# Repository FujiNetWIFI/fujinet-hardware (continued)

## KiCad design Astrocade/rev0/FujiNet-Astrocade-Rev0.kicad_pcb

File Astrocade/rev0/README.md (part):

# FujiNet-Astrocade Rev0

All-in-one **Bally Astrocade FujiNet cartridge**: one board in an Astrocade
cassette shell carrying both halves of the Astrocade FujiNet stack.

- **RP2354A** (RP2350A die + 2 MB flash in the package, QFN-60) runs the
  `fujicade` cart firmware from `fujinet-firmware/pico/astrocade`, board
  **`fujicade_rp2354`**. It serves the 8K cart window and the FujiNet
  mailbox straight off the 5 V bus through its 5 V-tolerant pads, with **no
  level shifters**. The pads tolerate 5 V only while IOVDD is powered, so the
  whole RP runs from its own fast LDO (see *Power*).
- **ESP32-S3-WROOM-1-N16R8** runs the **`fujiversal-astrocade`** build of
  fujinet-firmware. The two chips link **on the board over native USB**: the
  S3 is the USB *host* (IO19/IO20) and the RP a CDC device (VID 0xCafe).
  The S3 embeds the RP image and re-flashes it over PICOBOOT whenever it
  changes (`build_pico.py`).
- **USB-C** carries power plus a CP2102N UART with UMH3N auto-program
  (ESP32-S3-DevKitC-1 style) for flashing the S3.
- **microSD** (push-push, SPI on S3 IO38-41). Card detect on IO42 reads
  **low with a card in** (TF-015 drawing: the CD switch closes to the shell).
- **WS2812B-2020** status LED under a light pipe, on **+5V**: its datasheet
  rates VDD 3.7-5.3 V. VIH min is 2.7 V, so the S3's 3.3 V data drives it
  without a level shifter.
- **Buttons:** top-face **RESET** (SW4, resets the RP and the S3), **BOOTSEL**
  pinhole (SW1), S3 **EN/BOOT** (SW2/SW3, board-level).

This revision was audited with kicad-happy and the manufacturer datasheets,
and then redone. The schematic, board and fabrication files are all generated
from `tools/` (see *Regenerating*). The audit is
[`docs/design-review-rev0.md`](docs/design-review-rev0.md).

## Schematic

The schematic is drawn the way the later carts' (2600 Rev1, 7800, SMS, 5200) are:
- **every sheet is the board turned edge-left**: board south -> page left, north -> right, west -> top, east -> bottom;
- each part sits where it is on the board, and `tools/sch_place.py` checks the order;
- **every connection on a sheet is a wire**, flowing left to right from the console to the USB-C.

| Page | Sheet | Contents |
|---|---|---|
| 1 | root | The board outline at 2:1 with each sheet's block over its region; the nine signals between sheets wired; notes |
| 2 | `cart-bus` | The 26-land edge **straight into the RP2354A's GPIO unit**: 22 parallel wires (/CCS, A0-A12, D0-D7), no buffers; /CCS pull-up, the VSENSE divider, activity LED, SELFTEST / DBG_TX pads |
| 3 | `rp-core` | The RP2354A's core unit: every supply pin with its capacitor, the core regulator corner, crystal, SWD, RUN / BOOTSEL / RESET, the USB pair to the S3 |
| 4 | `fujinet` | ESP32-S3, EN / BOOT, microSD, WS2812 status LED |
| 5 | `usb` | USB-C, ESD, CP2102N, esptool's auto-program pair |
| 6 | `power` | Console 5 V / USB VBUS diode-OR, 3.3 V buck, RP LDO |

Rails are power symbols (`CONS_5V`, `VBUS`, `+5V`, `+3V3`, `+3V3_RP`, `DVDD`, `GND`). Sheets join only through hierarchical labels, wired on the root. KiCad names the nets:
- `/cart-bus/CA0` for a net local to its sheet;
- `/S3_EN` for a net joined on the root;
- `GND` for a rail.

The names are frozen in `tools/nets.lock` because the routed board carries them. References are frozen in `tools/refs.lock`.

## Edge port

The cassette edge carries **A0-A12, D0-D7, one pre-decoded active-low
Enable (/CCS), +5V and 3x GND**. There is no /RD, /WR, clock or reset, and
the console only ever *reads* the cart. The RP pin map is exactly
`astrocade_cart.h`:

| RP2354A | Net | Edge (Tilton 1-26) |
|---|---|---|
| GP0-GP12 | CA0-CA12 | A0 9, A1 8, A2 7, A3 6, A4 5, A5 4, A6 3, A7 2, A8 24, A9 23, A10 20, A11 19, A12 22 |
| GP13 | CCS_N (10k pull-up to +3V3_RP) | 21 |
| GP14-GP21 | CD0-CD7 | D0 10, D1 11, D2 12, D3 14, D4 15, D5 16, D6 17, D7 18 |
| GP26 | VSENSE: edge +5V (CONS_5V) through 10k/15k (3.0 V; 6 kOhm, below RP2350-E9's 8.2 kOhm) | 25 |
| GP22 / GP27 | SELFTEST / DBG_TX test pads | - |
| GP25 | green activity LED (330R) | - |

`tools/audit/edge_orientation.py` checks the generated board: land 1 is
**east** in KiCad top view, on B.Cu. That matches Tilton's "looking at the
cart slot, pins 1 to 26 left to right" with the cart inserted label-up.

**The unbuffered bus is safe because the firmware gates it.** The core1 loop
serves a read only while `(pins & SERVE_MASK) == SERVE_WANT`: /CCS low
**and** VSENSE high (`FUJICADE_VSENSE_PIN`). VSENSE is sensed on the console
side of the OR diode. So a cart on USB power in an **unpowered** console
never drives D0-D7 into it, and the loop lets go if the console loses power
mid-cycle. The bus pads' pull-downs are disabled (`FUJICADE_BUS_NO_PULLS`,
RP2350-E9).

The S3 pins follow `include/pinmap/fujiversal-astrocade.h`:

| S3 | Function |
|---|---|
| IO38/39/40/41 | SD MOSI / SCK / MISO / CS |
| IO42 | SD card detect (10k pull-up, low = card present) |
| IO48 | WS2812 (330R) |
| IO4 / IO5 | `PIN_RP2040_RUN` / `PIN_RP2040_BOOTSEL`, 1k each to RP RUN / QSPI_SS |
| IO19 / IO20 | USB D- / D+ to the RP (27R series) |
| TXD0 / RXD0 | CP2102N |

**Why RUN/BOOTSEL are direct 1k links.** `fnPicoUpdater::forceBootselViaPins()`
drives these pins **low** to assert and leaves them as inputs when idle. An
NPN driver (as on INTV Rev0) would invert that. Both chips run at 3.3 V
(`+3V3` and `+3V3_RP`), so a series resistor is the whole interface.

## Power

| Rail | Source | Feeds |
|---|---|---|
| `CONS_5V` | edge land 25 | OR diode, VSENSE divider |
| `VBUS` | USB-C (1 uF + 100 nF, ESD) | OR diode, CP2102N VBUS sense |
| `+5V` | SS34 diode-OR of CONS_5V and VBUS | buck, RP LDO, WS2812 |
| `+3V3` | AP63203 3.3 V / 2 A buck (6.8 uH) | ESP32-S3, CP2102N, microSD |
| `+3V3_RP` | **AP2112K-3.3 LDO** | every RP2354A supply: IOVDD x6, QSPI_IOVDD, USB_OTP_VDD, ADC_AVDD, VREG_VIN, VREG_AVDD (33R / 4.7 uF) |
| `DVDD` | RP2350 core SMPS (3.3 uH AOTA) | RP core, 1.1 V |

- **Why the RP has its own LDO.** The RP2350 datasheet says the GPIOs tolerate
  5.5 V "provided IOVDD is powered to 3.3 V" (p.1332). The first Rev0 fed IOVDD
  from the buck. The buck stays off until its UVLO, then soft-starts over
  4 ms, which left the pads unpowered while the console drove the bus. The
  AP2112K sits in dropout while the console rail rises, so +3V3_RP follows it.
  Following 1 V/ms into the rail's 21 uF needs 21 mA, under the 50 mA
  fold-back limit. A hot-plug step would take up to 1.4 ms, but hot-plugging
  isn't supported. Bring-up item 2 scopes it.
- **Supply order.** VREG_VIN and VREG_AVDD must rise together (p.402), and both
  are on the LDO.
- **Headroom.** At a 4.75 V console rail, +5V is at least 4.37 V after the
  diode. That clears the buck (3.8 V), the LDO (3.55 V) and the WS2812
  (3.7 V). There is no 5 V logic on the board. Numbers in
  `tools/audit/por_window.py`.

## Mechanics: a cassette, not a finger cart

A Videocade is a closed cassette-style box lying label-up in an **open-top
well**. The console's 26-contact **blade** (0.100" pitch, about 74 mm wide
and 3.6-3.8 mm thick, reaching about 17-18 mm in) enters a slot in the
leading face. It presses **up** against gold lands on the **PCB underside**.

The sourced dossier is `case/case-spec.md`, and the parametric shell is
`case/FujiNet-Astrocade-Shell.scad`. Its openings come from
`case/board-anchors.scad`, which is generated from the placement.

**Board:**

| | |
|---|---|
| Outline | 96 x 58 x 1.6 mm (x 52..148, y 30..88), 4x M3 NPTH for the shell posts |
| Contact lands | 26 x (1.7 x 14 mm) on **B.Cu only**, 2.54 mm pitch, 63.5 mm span, centred; land 1 is **east** in top view |
| Blade strip | B.Cu rule area over the south 16.5 mm (y >= 71.5): no tracks, vias or pour where the blade wipes |
| Land escapes | Each land's footprint carries a 0.5 mm neck under solder mask to a 0.3/0.6 mm plated hole **17.4 mm** in from the edge, beyond the blade's reach |
| Stack-up | **6 layers, 1.6 mm** (JLC06161H-2116 class): F.Cu signals + GND pour / In1.Cu **GND plane** / In2.Cu + In3.Cu signals / In4.Cu **power plane**: +3V3, a +3V3_RP island under the RP2354A region, a DVDD island under its core / B.Cu signals + GND pour (outside the blade strip). 4 layers was tried first and did not close (see *Status*) |
| Trailing edge (y=30) | USB-C (shell face 0.45 mm past the edge, HRO's recommended PCB-edge position), microSD slot (face 0.05 mm inside), and the ESP32-S3 antenna overhanging about 6.4 mm (shell antenna window) |
| Top face | SW4 RESET, SW1 BOOTSEL pinhole, D3 WS2812 light pipe |
| Assembly | 3 fiducials (FID1-3, 1 mm copper / 2 mm mask), all SMD parts on the top side |

## Flashing

- **ESP32-S3:** plug in the USB-C port (CP2102N, esptool auto-program) and run
  `pio run -e fujiversal-astrocade -t upload`. The build also compiles the
  RP firmware (`pico_src = pico/astrocade/firmware`,
  `pico_board = fujicade_rp2354`) and embeds it.
- **RP2354A:** flashed by the S3 at boot, over PICOBOOT. It tries the
  cooperative mailbox BOOTSEL doorbell first, else hardware forcing (IO5
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
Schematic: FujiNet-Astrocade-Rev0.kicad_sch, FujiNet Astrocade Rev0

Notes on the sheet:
edge lands: the console slot
FujiNet for the Bally Astrocade, Rev0: RP2354A on the cart bus + ESP32-S3. This page is the board seen from its component side, turned so that the edge (the 26 contact lands) faces left (board south -> page left, north -> right, west -> top, east -> bottom), 2:1, each sheet's block where its circui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

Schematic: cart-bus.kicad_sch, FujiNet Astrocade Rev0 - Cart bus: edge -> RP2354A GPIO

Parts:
D1: green; LED_0603_1608Metric; MPN KT-0603G; LCSC C12624
J1: Astrocade_Cart_Edge_26
R8, R9: 10k; R_0603_1608Metric; MPN 0603WAF1002T5E; LCSC C25804
R10: 15k; R_0603_1608Metric; MPN 0603WAF1502T5E; LCSC C22809
R13: 330R; R_0603_1608Metric; MPN 0603WAF3300T5E; LCSC C23138
TP4: SELFTEST; TestPoint_Pad_D1.5mm
TP5: DBG_TX; TestPoint_Pad_D1.5mm
U1: RP2354A; RPI_RP2350A_QFN60; MPN RP2354A; LCSC C41378174

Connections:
+3V3_RP: R8.1; also elsewhere on the board
/cart-bus/CA0: J1.9 (A0), U1.2 (GPIO0)
/cart-bus/CA1: J1.8 (A1), U1.3 (GPIO1)
/cart-bus/CA2: J1.7 (A2), U1.4 (GPIO2)
/cart-bus/CA3: J1.6 (A3), U1.5 (GPIO3)
/cart-bus/CA4: J1.5 (A4), U1.7 (GPIO4)
/cart-bus/CA5: J1.4 (A5), U1.8 (GPIO5)
/cart-bus/CA6: J1.3 (A6), U1.9 (GPIO6)
/cart-bus/CA7: J1.2 (A7), U1.10 (GPIO7)
/cart-bus/CA8: J1.24 (A8), U1.12 (GPIO8)
/cart-bus/CA9: J1.23 (A9), U1.13 (GPIO9)
/cart-bus/CA10: J1.20 (A10), U1.14 (GPIO10)
/cart-bus/CA11: J1.19 (A11), U1.15 (GPIO11)
/cart-bus/CA12: J1.22 (A12), U1.16 (GPIO12)
/cart-bus/CCS_N: J1.21 (~CCS), R8.2, U1.17 (GPIO13)
/cart-bus/CD0: J1.10 (D0), U1.18 (GPIO14)
/cart-bus/CD1: J1.11 (D1), U1.19 (GPIO15)
/cart-bus/CD2: J1.12 (D2), U1.27 (GPIO16)
/cart-bus/CD3: J1.14 (D3), U1.28 (GPIO17)
/cart-bus/CD4: J1.15 (D4), U1.29 (GPIO18)
/cart-bus/CD5: J1.16 (D5), U1.31 (GPIO19)
/cart-bus/CD6: J1.17 (D6), U1.32 (GPIO20)
/cart-bus/CD7: J1.18 (D7), U1.33 (GPIO21)
/cart-bus/RP_DBG_TX: TP5.1, U1.41 (GPIO27/ADC1)
/cart-bus/RP_LED: R13.1, U1.37 (GPIO25)
/cart-bus/RP_LED_A: D1.2 (A), R13.2
/cart-bus/SELFTEST: TP4.1, U1.34 (GPIO22)
/cart-bus/VSENSE: R9.2, R10.1, U1.40 (GPIO26/ADC0)
CONS_5V: J1.25 (+5V), R9.1; also elsewhere on the board
GND: D1.1 (K), J1.1 (GND), J1.13 (GND), J1.26 (GND), R10.2; also elsewhere on the board

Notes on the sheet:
The Bally Astrocade cassette port: 26 contact lands on the PCB underside (the console blade presses up), Tilton 1-26. No buffers: the RP2354A's fault-tolerant pads take 5.5 V while IOVDD is up, and +3V3_RP (power sheet, an LDO) rises with the console rail. A0-A12 = GPIO0-12, /CCS (the pre-decoded e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

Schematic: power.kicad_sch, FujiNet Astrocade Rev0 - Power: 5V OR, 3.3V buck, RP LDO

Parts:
C28, C32, C33: 100nF; C_0603_1608Metric; MPN CC0603KRX7R9BB104; LCSC C14663
C29, C30, C31, C34, C35: 22uF; C_0805_2012Metric; MPN CL21A226MAQNNNE; LCSC C45783
C36, C37: 1uF; C_0603_1608Metric; MPN CL10A105KB8NNNC; LCSC C15849
D7, D8: SS34; D_SMA; MPN SS34; LCSC C8678
L2: 6.8uH; L_Sunlord_SWPA4030S; MPN SWPA4030S6R8MT; LCSC C62684
TP8: +5V; TestPoint_Pad_D1.5mm
TP9: +3V3; TestPoint_Pad_D1.5mm
TP10: +3V3_RP; TestPoint_Pad_D1.5mm
U5: AP63203WU; TSOT-23-6; MPN AP63203WU-7; LCSC C780769
U6: AP2112K-3.3; SOT-23-5; MPN AP2112K-3.3TRG1; LCSC C51118

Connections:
+3V3: C34.1, C35.1, L2.2, TP9.1, U5.1 (FB); also elsewhere on the board
+3V3_RP: C37.1, TP10.1, U6.5 (VOUT); also elsewhere on the board
+5V: C29.1, C30.1, C31.1, C32.1, C36.1, D7.1 (K), D8.1 (K), TP8.1, U5.2 (EN), U5.3 (IN), U6.1 (VIN), U6.3 (EN); also elsewhere on the board
/power/BUCK_BST: C33.2, U5.6 (BST)
/power/BUCK_SW: C33.1, L2.1, U5.5 (SW)
CONS_5V: C28.1, D7.2 (A); also elsewhere on the board
GND: C28.2, C29.2, C30.2, C31.2, C32.2, C34.2, C35.2, C36.2, C37.2, U5.4 (GND), U6.2 (GND); also elsewhere on the board
VBUS: D8.2 (A); also elsewhere on the board

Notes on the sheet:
PWR_FLAG: these rails reach their loads only through passive parts (the edge land, USB-C, the SS34s, the buck's inductor).
Power tree: +5V is the OR of two sources, so neither can back-feed the other. CONS_5V edge land 25, the console's +5V, through D7 SS34. VBUS USB-C, through D8 SS34. SS34 VF ~0.35 V at the cart's ~0.4 A: +5V is 4.4-4.9 V; there is no 5 V logic on this board. U6 AP2112K-3.3 LDO -> +3V3_RP: the WHOLE 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

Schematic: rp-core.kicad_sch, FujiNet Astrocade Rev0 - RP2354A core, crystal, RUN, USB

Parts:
C1, C2, C3, C4, C5, C6, C7, C9, C12, C13, C14: 100nF; C_0603_1608Metric; MPN CC0603KRX7R9BB104; LCSC C14663
C8: 100nF; RPI_C0402; MPN CL05B104KO5NNNC; LCSC C1525
C10, C15: 4.7uF; RPI_C0402_wide; MPN CL05A475MP5NRNC; LCSC C23733
C11: 10uF; C_0603_1608Metric; MPN CL10A106KP8NNNC; LCSC C19702
C16: 4.7uF; RPI_C0402; MPN CL05A475MP5NRNC; LCSC C23733
C17, C18: 15pF; C_0603_1608Metric; MPN CL10C150JB8NNNC; LCSC C1644
D2: BAT54C; SOT-23; MPN BAT54C,215; LCSC C37704
L1: 3.3uH; RPI_L_AOTA-B201610S3R3; MPN AOTA-B201610S3R3-101-T; LCSC C42411119
R1: 33R; RPI_R0402; MPN 0402WGF330JTCE; LCSC C25105
R2, R5, R6, R7: 1k; R_0603_1608Metric; MPN 0603WAF1001T5E; LCSC C21190
R3, R4: 10k; R_0603_1608Metric; MPN 0603WAF1002T5E; LCSC C25804
R11, R12: 27R; RPI_R0402; MPN 0402WGF270JTCE; LCSC C25100
SW1: BOOTSEL; SW_SPST_TL3342; MPN TL3342F160QG; LCSC C2886898
SW4: RESET; SW_SPST_TL3342; MPN TL3342F160QG; LCSC C2886898
TP1: SWCLK; TestPoint_Pad_D1.5mm
TP2: SWDIO; TestPoint_Pad_D1.5mm
TP3: GND; TestPoint_Pad_D1.5mm
TP6: RUN; TestPoint_Pad_D1.5mm
TP7: BOOTSEL; TestPoint_Pad_D1.5mm
U1: RP2354A; RPI_RP2350A_QFN60; MPN RP2354A; LCSC C41378174
Y1: 12MHz; Crystal_SMD_3225-4Pin_3.2x2.5mm; MPN ABM8-272-T3; LCSC C20625731

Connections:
+3V3_RP: C1.1, C2.1, C3.1, C4.1, C5.1, C6.1, C7.1, C8.1, C9.1, C10.1, C11.1, R1.1, R3.1, R4.1, U1.1 (IOVDD), U1.11 (IOVDD), U1.20 (IOVDD), U1.30 (IOVDD), U1.38 (IOVDD), U1.44 (ADC_AVDD), U1.45 (IOVDD), U1.49 (VREG_VIN), U1.53 (USB_OTP_VDD), U1.54 (QSPI_IOVDD); also elsewhere on the board
/BOOTSEL_CTL: R7.1; also elsewhere on the board
/RUN_CTL: R6.1; also elsewhere on the board
/S3_EN: D2.2; also elsewhere on the board
/USB_DM: R12.1; also elsewhere on the board
/USB_DP: R11.1; also elsewhere on the board
/rp-core/BOOTSEL_BTN: R5.2, SW1.1
/rp-core/QSPI_SS: R4.2, R5.1, R7.2, TP7.1, U1.60 (~QSPI_SS)
/rp-core/RP_LX: L1.2, U1.48 (VREG_LX)
/rp-core/RP_USB_DM: R12.2, U1.51 (USB_DM)
/rp-core/RP_USB_DP: R11.2, U1.52 (USB_DP)
/rp-core/RST_BTN: D2.3, SW4.1
/rp-core/RUN: D2.1, R3.2, R6.2, TP6.1, U1.26 (RUN)
/rp-core/SWCLK: TP1.1, U1.24 (SWCLK)
/rp-core/SWDIO: TP2.1, U1.25 (SWDIO)
/rp-core/VREG_AVDD: C16.1, R1.2, U1.46 (VREG_AVDD)
/rp-core/XIN: C17.1, U1.21 (XIN), Y1.1
/rp-core/XOUT: R2.1, U1.22 (XOUT)
/rp-core/XOUT_Y: C18.1, R2.2, Y1.3
DVDD: C12.1, C13.1, C14.1, C15.1, L1.1, U1.6 (DVDD), U1.23 (DVDD), U1.39 (DVDD), U1.50 (VREG_FB)
GND: C1.2, C2.2, C3.2, C4.2, C5.2, C6.2, C7.2, C8.2, C9.2, C10.2, C11.2, C12.2, C13.2, C14.2, C15.2, C16.2, C17.2, C18.2, SW1.2, SW4.2, TP3.1, U1.47 (VREG_PGND), U1.61 (GND), Y1.2 (G), Y1.4 (G); also elsewhere on the board

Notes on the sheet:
Supplies (RP2350 datasheet 6.3.7): IOVDD, QSPI_IOVDD, USB_OTP_VDD, ADC_AVDD and VREG_VIN on +3V3_RP, the AP2112K LDO that rises with +5V; the core regulator switches VREG_LX through 3.3 uH onto DVDD (VREG_FB senses it), its analog supply VREG_AVDD through 33R / 4.7 uF. One 100 nF at every supply pi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

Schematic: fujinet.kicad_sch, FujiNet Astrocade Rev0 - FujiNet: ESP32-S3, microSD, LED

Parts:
C19: 22uF; C_0805_2012Metric; MPN CL21A226MAQNNNE; LCSC C45783
C20, C23: 100nF; C_0603_1608Metric; MPN CC0603KRX7R9BB104; LCSC C14663
C21: 1uF; C_0603_1608Metric; MPN CL10A105KB8NNNC; LCSC C15849
C22: 10uF; C_0603_1608Metric; MPN CL10A106KP8NNNC; LCSC C19702
D3: WS2812B-2020-V6; LED_WS2812B-2020_PLCC4_2.0x2.0mm; MPN WS2812B-2020-V6; LCSC C52917434
J2: microSD; TF-SMD_TF-015; MPN TF-015; LCSC C113206
R14, R15: 10k; R_0603_1608Metric; MPN 0603WAF1002T5E; LCSC C25804
R16: 330R; R_0603_1608Metric; MPN 0603WAF3300T5E; LCSC C23138
RN1: 4x10k; R_Array_Convex_4x0603; MPN 4D03WGJ0103T5E; LCSC C29718
SW2: S3_RST; SW_SPST_TL3342; MPN TL3342F160QG; LCSC C2886898
SW3: S3_BOOT; SW_SPST_TL3342; MPN TL3342F160QG; LCSC C2886898
U2: ESP32-S3-WROOM-1-N16R8; ESP32-S3-WROOM-1; MPN ESP32-S3-WROOM-1-N16R8; LCSC C2913202

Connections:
+3V3: C19.1, C20.1, C22.1, J2.4 (VDD), R14.1, R15.1, RN1.5 (R4.2), RN1.6 (R3.2), RN1.7 (R2.2), RN1.8 (R1.2), U2.2 (3V3); also elsewhere on the board
+5V: C23.1, D3.4 (VDD); also elsewhere on the board
/BOOTSEL_CTL: U2.5 (IO5); also elsewhere on the board
/RUN_CTL: U2.4 (IO4); also elsewhere on the board
/S3_EN: C21.1, R14.2, SW2.1, U2.3 (EN); also elsewhere on the board
/S3_IO0: SW3.1, U2.27 (IO0); also elsewhere on the board
/S3_RXD: U2.36 (RXD0); also elsewhere on the board
/S3_TXD: U2.37 (TXD0); also elsewhere on the board
/USB_DM: U2.13 (USB_D-); also elsewhere on the board
/USB_DP: U2.14 (USB_D+); also elsewhere on the board
/fujinet/LED_STRIP: R16.1, U2.25 (IO48)
/fujinet/SD_CD: J2.9 (CD), R15.2, U2.35 (IO42)
/fujinet/SD_CS: J2.2 (DAT3/CS), RN1.1 (R1.1), U2.34 (IO41)
/fujinet/SD_DAT1: J2.8 (DAT1), RN1.3 (R3.1)
/fujinet/SD_DAT2: J2.1 (DAT2), RN1.4 (R4.1)
/fujinet/SD_MISO: J2.7 (DAT0/DO), RN1.2 (R2.1), U2.33 (IO40)
/fujinet/SD_MOSI: J2.3 (CMD/DI), U2.31 (IO38)
/fujinet/SD_SCK: J2.5 (CLK), U2.32 (IO39)
/fujinet/WS_DIN: D3.3 (DIN), R16.2
GND: C19.2, C20.2, C21.2, C22.2, C23.2, D3.2 (VSS), J2.6 (VSS), J2.10 (SH), J2.11 (SH), J2.12 (SH), J2.13 (SH), SW2.2, SW3.2, U2.1 (GND), U2.40 (GND), U2.41 (GND); also elsewhere on the board

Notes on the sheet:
ESP32-S3-WROOM-1-N16R8: the FujiNet (fujiversal-astrocade.h pin map). EN: 10k / 1 uF power-on delay. The S3_RST button, the cart RESET (rp-core, through the BAT54C) and the USB bridge's auto-program pair (usb sheet) all pull it low; S3_BOOT and the same pair pull IO0. IO4 / IO5 drive the RP2354A's 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

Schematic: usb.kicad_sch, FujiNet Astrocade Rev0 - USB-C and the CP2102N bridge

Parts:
C24: 1uF; C_0603_1608Metric; MPN CL10A105KB8NNNC; LCSC C15849
C25, C26: 100nF; C_0603_1608Metric; MPN CC0603KRX7R9BB104; LCSC C14663
C27: 4.7uF; C_0603_1608Metric; MPN CL10A475KO8NNNC; LCSC C19666
D4, D5, D6: ESD5Z5.0T1G; D_SOD-523; MPN ESD5Z5.0T1G; LCSC C82044
J3: USB-C; USB_C_Receptacle_HRO_TYPE-C-31-M-12; MPN TYPE-C-31-M-12; LCSC C165948
R17, R18: 5.1k; R_0603_1608Metric; MPN 0603WAF5101T5E; LCSC C23186
R19: 22k; R_0603_1608Metric; MPN 0603WAF2202T5E; LCSC C31850
R20: 47k; R_0603_1608Metric; MPN 0603WAF4702T5E; LCSC C25819
R21: 10k; R_0603_1608Metric; MPN 0603WAF1002T5E; LCSC C25804
U3: CP2102N-A02-GQFN28; QFN-28-1EP_5x5mm_P0.5mm_EP3.35x3.35mm; MPN CP2102N-A02-GQFN28R; LCSC C964632
U4: UMH3N; SOT-363_SC-70-6; MPN UMH3N; LCSC C62892

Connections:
+3V3: C26.1, C27.1, R21.1, U3.6 (VDD), U3.7 (VREGIN); also elsewhere on the board
/S3_EN: U4.6 (C1); also elsewhere on the board
/S3_IO0: U4.3 (C2); also elsewhere on the board
/S3_RXD: U3.26 (TXD); also elsewhere on the board
/S3_TXD: U3.25 (RXD); also elsewhere on the board
/usb/CC1: J3.A5 (CC1), R17.1
/usb/CC2: J3.B5 (CC2), R18.1
/usb/CP_RST: R21.2, U3.9 (~RST)
/usb/UART_DTR: U3.28 (~DTR), U4.2 (B1), U4.4 (E2)
/usb/UART_RTS: U3.24 (~RTS), U4.1 (E1), U4.5 (B2)
/usb/UBRG_DM: D5.1 (K), J3.A7 (D-), J3.B7 (D-), U3.5 (D-)
/usb/UBRG_DP: D4.1 (K), J3.A6 (D+), J3.B6 (D+), U3.4 (D+)
/usb/VBUS_SNS: R19.2, R20.1, U3.8 (VBUS)
GND: C24.2, C25.2, C26.2, C27.2, D4.2 (A), D5.2 (A), D6.2 (A), J3.A1 (GND), J3.A12 (GND), J3.B1 (GND), J3.B12 (GND), J3.SH (SHIELD), R17.2, R18.2, R20.2, U3.3 (GND), U3.23 (~CTS), U3.29 (GND); also elsewhere on the board
VBUS: C24.1, C25.1, D6.1 (K), J3.A4 (VBUS), J3.A9 (VBUS), J3.B4 (VBUS), J3.B9 (VBUS), R19.1; also elsewhere on the board

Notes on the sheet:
esptool's auto-program pair, as on the ESP32-S3-DevKitC-1: DTR low with RTS high pulls EN low; RTS low with DTR high pulls IO0 low; both high or both low leave the S3 alone.

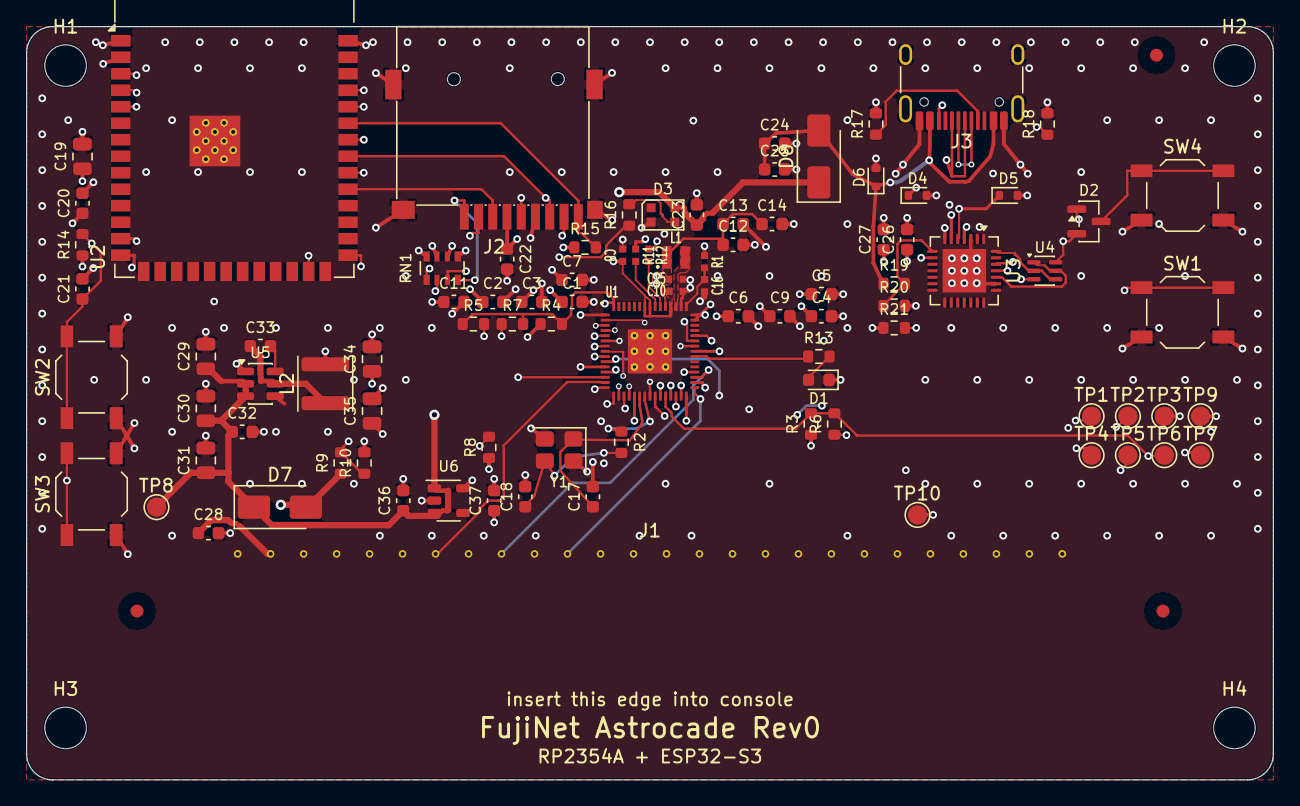
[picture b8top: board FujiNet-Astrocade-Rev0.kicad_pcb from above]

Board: 6 copper layers, 96.0 x 58.0 mm, 100 parts (0 on the bottom side), 74 nets.

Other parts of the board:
FID1, FID2, FID3: Fiducial_1mm_Mask2mm
H1, H2, H3, H4: M3; MountingHole_3.2mm_NPTH

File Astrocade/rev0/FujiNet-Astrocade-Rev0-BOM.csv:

"Refs","Value","Footprint","MPN","LCSC","Description","DNP"
"C1,C2,C3,C4,C5,C6,C7,C9,C12,C13,C14,C20,C23,C25,C26,C28,C32,C33","100nF","C_0603_1608Metric","CC0603KRX7R9BB104","C14663","IOVDD decoupling",""
"C8","100nF","RPI_C0402","CL05B104KO5NNNC","C1525","USB_OTP_VDD + QSPI_IOVDD decoupling",""
"C10,C15","4.7uF","RPI_C0402_wide","CL05A475MP5NRNC","C23733","VREG_VIN bulk",""
"C11,C22","10uF","C_0603_1608Metric","CL10A106KP8NNNC","C19702","RP 3V3 bulk",""
"C16","4.7uF","RPI_C0402","CL05A475MP5NRNC","C23733","VREG_AVDD filter",""
"C17,C18","15pF","C_0603_1608Metric","CL10C150JB8NNNC","C1644","crystal load",""
"C19,C29,C30,C31,C34,C35","22uF","C_0805_2012Metric","CL21A226MAQNNNE","C45783","S3 bulk (WiFi TX bursts)",""
"C21,C24,C36,C37","1uF","C_0603_1608Metric","CL10A105KB8NNNC","C15849","EN power-on delay",""
"C27","4.7uF","C_0603_1608Metric","CL10A475KO8NNNC","C19666","CP2102N VDD bulk",""
"D1","green","LED_0603_1608Metric","KT-0603G","C12624","RP activity LED",""
"D2","BAT54C","SOT-23","BAT54C,215","C37704","RESET steering, common cathode",""
"D3","WS2812B-2020-V6","LED_WS2812B-2020_PLCC4_2.0x2.0mm","WS2812B-2020-V6","C52917434","status LED on +5V (datasheet VDD 3.7-5.3 V; VIH 2.7 V takes 3.3 V data)",""
"D4,D5,D6","ESD5Z5.0T1G","D_SOD-523","ESD5Z5.0T1G","C82044","ESD",""
"D7,D8","SS34","D_SMA","SS34","C8678","console 5V OR-ing",""
"J2","microSD","TF-SMD_TF-015","TF-015","C113206","microSD push-push, SPI mode",""
"J3","USB-C","USB_C_Receptacle_HRO_TYPE-C-31-M-12","TYPE-C-31-M-12","C165948","power + S3 programming",""
"L1","3.3uH","RPI_L_AOTA-B201610S3R3","AOTA-B201610S3R3-101-T","C42411119","RP2350 core SMPS inductor",""
"L2","6.8uH","L_Sunlord_SWPA4030S","SWPA4030S6R8MT","C62684","buck inductor",""
"R1","33R","RPI_R0402","0402WGF330JTCE","C25105","VREG_AVDD filter",""
"R2,R5,R6,R7","1k","R_0603_1608Metric","0603WAF1001T5E","C21190","crystal drive limit",""
"R3,R4,R8,R9,R14,R15,R21","10k","R_0603_1608Metric","0603WAF1002T5E","C25804","RUN pull-up",""
"R10","15k","R_0603_1608Metric","0603WAF1502T5E","C22809","console 5V sense -> 3.0V (6 kOhm: beats RP2350-E9)",""
"R11,R12","27R","RPI_R0402","0402WGF270JTCE","C25100","USB series",""
"R13,R16","330R","R_0603_1608Metric","0603WAF3300T5E","C23138","LED series (KT-0603G VF ~2.6-2.85 V: 1.5-2 mA from 3.3 V)",""
"R17,R18","5.1k","R_0603_1608Metric","0603WAF5101T5E","C23186","UFP Rd",""
"R19","22k","R_0603_1608Metric","0603WAF2202T5E","C31850","VBUS sense divider",""
"R20","47k","R_0603_1608Metric","0603WAF4702T5E","C25819","VBUS sense divider",""
"RN1","4x10k","R_Array_Convex_4x0603","4D03WGJ0103T5E","C29718","SD pull-ups",""
"SW1","BOOTSEL","SW_SPST_TL3342","TL3342F160QG","C2886898","RP2354 BOOTSEL (hold while pressing RESET)",""
"SW2","S3_RST","SW_SPST_TL3342","TL3342F160QG","C2886898","ESP32-S3 EN",""
"SW3","S3_BOOT","SW_SPST_TL3342","TL3342F160QG","C2886898","ESP32-S3 BOOT (IO0)",""
"SW4","RESET","SW_SPST_TL3342","TL3342F160QG","C2886898","cart RESET: RP RUN + S3 EN via BAT54C",""
"U1","RP2354A","RPI_RP2350A_QFN60","RP2354A","C41378174","RP2350A + 2MB flash in package; cart bus server",""
"U2","ESP32-S3-WROOM-1-N16R8","ESP32-S3-WROOM-1","ESP32-S3-WROOM-1-N16R8","C2913202","FujiNet core (fujiversal-astrocade)",""
"U3","CP2102N-A02-GQFN28","QFN-28-1EP_5x5mm_P0.5mm_EP3.35x3.35mm","CP2102N-A02-GQFN28R","C964632","USB-UART for S3 flashing/console (self-powered)",""
"U4","UMH3N","SOT-363_SC-70-6","UMH3N","C62892","esptool auto-program (DevKitC-1 style)",""
"U5","AP63203WU","TSOT-23-6","AP63203WU-7","C780769","3.3V 2A buck",""
"U6","AP2112K-3.3","SOT-23-5","AP2112K-3.3TRG1","C51118","RP2354A 3.3V LDO (IOVDD, VREG_VIN, VREG_AVDD), fast start",""
"Y1","12MHz","Crystal_SMD_3225-4Pin_3.2x2.5mm","ABM8-272-T3","C20625731","",""

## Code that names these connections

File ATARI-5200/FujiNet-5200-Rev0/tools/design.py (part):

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RP_IO_RAIL = '+3V3_RP'     # IOVDD x8, QSPI_IOVDD, USB_OTP_VDD, ADC_AVDD: the fast LDO
RP_CORE_RAIL = RP_IO_RAIL  # VREG_VIN (+ VREG_AVDD through 33R) on the same LDO rail

# a52_cart.h.  GPIO0-31 are the 5 V-tolerant bus inputs; GPIO40-47 are not and carry only the ADC
# sense and the 3.3 V debug header.
RP_GPIO_NET = {i: 'A%d' % i for i in range(14)}                     # A0_PIN 0: A0-A13
RP_GPIO_NET.update({14: 'EN40_N', 15: 'EN80_N'})                    # EN40_PIN, EN80_PIN
RP_GPIO_NET.update({16 + i: 'RP_D%d' % i for i in range(8)})        # D0_PIN 16: into the '541
RP_GPIO_NET.update({24: 'PWR_OK', 25: 'PHI2_RP', 26: 'BUF_EN', 27: 'RP_LED', 28: 'ILK'})
RP_GPIO_NET.update({g: NC for g in range(29, 40)})
RP_GPIO_NET.update({40: 'VSENSE_ADC', 41: NC, 42: NC, 43: NC, 44: 'DBG_TX', 45: 'DBG_RX', 46: NC, 47: NC})
assert len(RP_GPIO_NET) == 48 and set(RP_GPIO_NET) == set(RP_GPIO_PIN)

# ESP32-S3-WROOM-1 module pad -> function (pads per the KiCad symbol)
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      70: NC, 71: NC, 72: NC, 73: NC, 74: NC,                                 # QSPI (flash in package)
      75: 'QSPI_SS', 81: 'GND'}
rp.update({p: RP_IO_RAIL for p in RP_IOVDD_PINS})
rp.update({p: 'DVDD' for p in RP_DVDD_PINS})
for g, pin in RP_GPIO_PIN.items():
    rp[pin] = RP_GPIO_NET[g]
U_RP = add('U', '%s:RP2354B_Split' % LIB, 'RP2354B', FP('QFN-80-1EP_10x10mm_P0.4mm_EP3.4x3.4mm'), rp,
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U_RP.unit_sheets = {1: 'cart-bus', 2: 'rp-core'}
U_RP.pin_unit = {str(pad): 1 if pad in RP_GPIO_PIN.values() else 2 for pad in rp}

# -- the data path: the RP puts each byte on GPIO16-23, a 74HCT541 that only the enables open puts
# it on D0-D7 (a52_cart.h: software is never between an enable and the data).  Its eight channels
# are identical, so they are used in reverse (bit k on channel 8-k: A8 / Y8 carry D0): turned 270
# degrees over the D0-D7 fingers, the '541's Y row (pins 11-18) then meets the fingers in their own
# left-to-right order and its A row (pins 9-2) the RP2354B's GPIO16-23 corner in theirs -- the data
# path from the slot to the RP crosses nothing (gen_pcb.buf_fanin draws the finger side).
buf = {1: 'SERVE_N', 19: 'EN_ANY_N', 10: 'GND', 20: '+5V'}     # /OE1, /OE2 (equivalent: drive = !OE1 & !OE2)
buf.update({9 - i: 'RP_D%d' % i for i in range(8)})             # A8..A1 (pins 9..2) = bit 0..7
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# -- PHI2 (edge 14): GND on CA018087; on the universal boards PHI2 through a 74LS125 and CR9 (1N914,
# anode at pin 14), so the console only pulls it low, to VOL(LS125) + VF(1N914) <= ~1.15 V: over the
# RP2350's VIL of 0.8 V (Table 1436).  A 74LVC1G17 Schmitt on +5V reads it (VT- >= 1.32 V at VCC
# 4.5 V, Nexperia 74LVC1G17 Table 8) and drives GPIO25 (5 V tolerant).  The pull-up comes from the
# console's own 5 V, so nothing is pushed into an unpowered console; 4.7k reaches VT+ in ~60 ns.
R('4.7k', 'CONS_5V', 'PHI2', desc='PHI2 pull-up (the console drives pin 14 only low, through a diode)',
  key='R_PHI2PU')
add('U', '74xGxx:74LVC1G17', '74LVC1G17', FP('SOT-353_SC-70-5'), {1: NC, 2: 'PHI2', 3: 'GND', 4: 'PHI2_RP',
    5: '+5V'}, mpn='74LVC1G17GW,125', lcsc='C426705', desc='PHI2 Schmitt buffer: CMOS thresholds for the '
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       key='JP_ILK')
# DNP: a firmware-controlled interlock (a console power cycle = its only reset).  The jumper sits at
# ground potential when closed, so the switch is an N-FET on the low side: D on CI2 (pin 36), S on CI1
# (pin 18), gate pulled up to +5V (closed whenever the cart has power); GPIO28 high turns Q_ILKDRV on
# and opens it.  Needs the cart powered from USB or the edge's raw DC once JP_ILK is cut.
NFET('ILK_G', 'ILK_A', 'ILK_B', 'interlock switch (DNP): D = CI2 (pin 36), S = CI1 (pin 18)', dnp=True,
     key='Q_ILK')
R('10k', '+5V', 'ILK_G', desc='interlock switch closed by default (DNP)', dnp=True, key='R_ILKG')
NFET('ILK', 'GND', 'ILK_G', 'interlock switch driver, G = GPIO28: high opens the interlock (DNP)', dnp=True,
     key='Q_ILKDRV')
R('4.7k', 'ILK', 'GND', desc='GPIO28 low until the firmware drives it (RP2350-E9: <= 8.2k; DNP)', dnp=True,
  key='R_ILKPD')
# -- VR1 (the console 5 V that feeds the cart) for the ADC (GPIO40, not 5 V tolerant): 100k / 100k =
# 0.5 x, 5.5 V reads 2.75 V; 100 nF for the ADC's sample capacitor
R('100k', 'CONS_5V', 'VSENSE_ADC', desc='console 5V -> ADC divider (0.5 x)', key='R_ADCH')
R('100k', 'VSENSE_ADC', 'GND', desc='console 5V -> ADC divider', key='R_ADCL')
C('100nF', 'VSENSE_ADC', desc='ADC sample reservoir', key='C_ADCF')
# -- activity LED straight off GPIO27 (3.3 V): red, ~1.3 mA
R('1k', 'RP_LED', 'RP_LED_A', desc='activity LED series', key='R_LED')
add('D', 'Device:LED', 'red', FP('LED_0603_1608Metric'), {1: 'GND', 2: 'RP_LED_A'},
    mpn='KT-0603R', lcsc='C2286', desc='activity LED (GPIO27)', key='D_LED')
# -- debug UART (GPIO44 TX, GPIO45 RX; 3.3 V only), DNP: fit for bring-up
add('J', 'Connector_Generic:Conn_01x03', 'DBG UART', FP('PinHeader_1x03_P2.54mm_Vertical'),
    {1: 'DBG_TX', 2: 'DBG_RX', 3: 'GND'}, mpn='PZ254V-11-03P', lcsc='C2937625',
    desc='RP debug UART, 3.3 V: 1 TX (GPIO44), 2 RX (GPIO45), 3 GND; fit for bring-up', dnp=True, key='J_DBG')
# -- bring-up pads: the enables, PHI2 and the '541's two enables, PWR_OK, with a scope ground
TP('EN40_N', '/EN40', desc='scope pad: console /Enable $40-$7F', key='TP_EN40')
TP('EN80_N', '/EN80', desc='scope pad: console /Enable $80-$BF', key='TP_EN80')
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C('10uF', RP_IO_RAIL, desc='RP IO rail bulk (LDO output)', key='C_IOBULK')
C('4.7uF', RP_CORE_RAIL, desc='VREG_VIN bulk (LDO rail)', key='C_VREGIN')
for pin in RP_DVDD_PINS:
    C('100nF', 'DVDD', desc='DVDD decoupling', key='C_DV%d' % pin)
C('4.7uF', 'DVDD', desc='core regulator output', key='C_DVBULK')
R('33R', RP_CORE_RAIL, 'VREG_AVDD', desc='VREG_AVDD filter', key='R_AVDD')
C('4.7uF', 'VREG_AVDD', desc='VREG_AVDD filter', key='C_AVDD')
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SW('RESET', 'RST_BTN', 'cart RESET: RP RUN + S3 EN via BAT54C', key='SW_RESET')
add('D', 'Diode:BAT54C', 'BAT54C', FP('SOT-23'), {1: 'RUN', 2: 'S3_EN', 3: 'RST_BTN'},
    mpn='BAT54C,215', lcsc='C37704', desc='RESET steering, common cathode', key='D_RST')
# RUN / BOOTSEL: the S3 drives them low to assert (fnPicoUpdater::forceBootselViaPins)
R('10k', RP_IO_RAIL, 'RUN', desc='RUN pull-up', key='R_RUN')
R('10k', RP_IO_RAIL, 'QSPI_SS', desc='QSPI_SS pull-up', key='R_SS')
R('1k', 'QSPI_SS', 'BOOTSEL_BTN', desc='BOOTSEL button series', key='R_BSEL')
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# -- edge 11: the raw DC.  A bridged jumper (cut it to take nothing from pin 11), a 0.35 A PTC so a
# fault on the cart never loads the adapter, 2.2R against the inrush into the buck's input when the
# cart goes in with the adapter live, the AP63205 (3.8-32 V in, 5 V 2 A), an SS34 onto +5V.
JUMPER('UNREG', 'UNREG_J', 'RAWDC', 'edge 11 raw DC input, closed (cut to take nothing from pin 11)',
       key='JP_UNREG')
add('F', 'Device:Polyfuse', '0.35A', FP('Fuse_1206_3216Metric'), {1: 'UNREG_J', 2: 'UNREG_F'},
    mpn='1206L035/30WR', lcsc='C2153989', desc='PTC 0.35 A hold, 30 V: the adapter is never loaded by a cart fault',
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
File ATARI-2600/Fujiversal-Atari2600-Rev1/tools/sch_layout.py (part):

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    P = lambda n: sh.P(U, n)
    gp = lambda g: sh.P(U, D.RP_GPIO_PIN[g])
    xg = gp(2)[0]                                       # the GPIO column (pin ends), facing left
    # ---- the edge, level with GPIO2..22
    jx = X - 78.74
    sh.place(J, jx, 0)
    jy = gp(2)[1] - sh.N(J, 'CA0')[1]                    # A0 level with GPIO2
    sh.place(J, jx, jy, fields='left')
    sh.sup(sh.P(J, 23), 'CONS_5V')
    g1, g2 = sh.P(J, 12), sh.P(J, 24)
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        y = by + 5.08 * k
        sh.bus((bx, y), (bx + 7.62, y))
        sh.glabel(Pt_(bx + 7.62, y, 1, 0), name, 'R', shape)
    # ---- debug UART (GPIO0/1) up to two test pads, above the bus
    for g, x, tp, fl in ((0, xg - 5.08, 'TP_TX', 'left'), (1, xg - 15.24, 'TP_RX', 'left')):
        p = gp(g)
        sh.wire(p, (x, p[1]), (x, Y - 50.8))
        sh.place(K[tp], x, Y - 50.8, fields=fl)
    sh.name((xg - 5.08, Y - 45.72), 'RP_TX', 'R', 'R')
    sh.name((xg - 15.24, Y - 45.72), 'RP_RX', 'L', 'L')
    # ---- below the bus: the activity LED (GPIO25) and the console 5 V sense (GPIO27)
    p = gp(25)
    x = xg - 12.7
    rl, dl = K['R_LED'], K['D_LED']
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    sh.name(sh.P(rl, 2), 'RP_LED_A', 'L', 'L')
    p = gp(27)
    sh.wire(p, (xg - 5.08, p[1]), (xg - 5.08, Y + 40.64))
    sh.glabel(Pt_(xg - 5.08, Y + 40.64, 0, 1), 'VSENSE', 'D', 'input')
    for g in (23, 24, 26, 28, 29):
        sh.nc(gp(g))
    # ---- supplies across the top: the +3V3_RP rail and its decoupling row (right),
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    sh.wire(*sorted({(q[0], ry) for q in rail_pins} | {(av[0], ry)} | {(x, ry) for x in xs}))
    sh.sup((rail_pins[0][0], ry), '+3V3_RP')
    # core regulator: LX up and left through the inductor, DVDD on to its caps;
    # FB and the DVDD pins join that node
    lx, fb, dv = P(48), P(50), P(6)
    ly = top - 25.4
    L = K['L_VREG']
    sh.place(L, lx[0] - 7.62, ly, rot=90, fields='below')         # pin 1 (DVDD) left, pin 2 (LX) right
    sh.wire(lx, (lx[0], ly), sh.P(L, 2))
    dcaps = [K[k] for k in ('C_VOUT', 'C_DVDD39', 'C_DVDD6', 'C_DVDD23')]
    node = (dv[0] - 10.16, ly)
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    sh.place(D1, xr + 20.32, ry_ - 7.62, rot=180, mirror='y', fields='below')   # A1 left, A2 right, K up
    sh.wire(pts[1], sh.P(D1, 1))
    sh.wire(sh.P(D1, 2), (col, sh.P(D1, 2)[1]))
    sh.glabel((col, sh.P(D1, 2)[1]), 'S3_EN', 'R', 'bidirectional')
    k = sh.P(D1, 3)
    sw = K['SW_RESET']
    sh.place(sw, xr + 27.94, ry_ - 17.78, fields='above')
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    sh.gnd((xr + 38.1, ry_ - 17.78))
    sh.name((k[0], ry_ - 15.24), 'RST_BTN', 'R', 'R')
    rc = K['R_RUNCTL']
    sh.place(rc, pts[2][0] + 3.81, ry_, rot=270, fields='above')     # pin 2 (RUN) left, pin 1 right
    sh.wire(pts[2], sh.P(rc, 2))
    sh.wire(sh.P(rc, 1), (col, ry_))
    sh.glabel((col, ry_), 'RUN_CTL', 'R', 'input')
    sh.name((xr + 2.54, ry_), 'RUN', 'D', 'R')
    # USB to the S3: 27R series pair
    for pin, r, net, rnet, d in ((51, 'R_USBM', 'USB_DM', 'RP_USB_DM', 'U'), (52, 'R_USBP', 'USB_DP', 'RP_USB_DP', 'D')):
        p = P(pin)
        rr = K[r]
        sh.place(rr, xr + 38.1, p[1], rot=270, fields='above' if pin == 51 else 'below')
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    sh.place(sc, pts[2][0] + 3.81, q, rot=270, fields='above')
    sh.wire(pts[2], sh.P(sc, 2))
    sh.wire(sh.P(sc, 1), (col, q))
    sh.glabel((col, q), 'BOOTSEL_CTL', 'R', 'input')
    for n in (55, 56, 57, 58, 59):
        sh.nc(P(n))
    # 12 MHz crystal: XIN straight to the crystal and its load cap, XOUT through the 1k
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    g2 = sh.P(Yc, 2)
    sh.wire(g2, (g2[0] + 2.54, g2[1]))
    sh.gnd((g2[0] + 2.54, g2[1]))
    sh.place(rx, xr + 10.16, xo[1], rot=90, fields='above')        # pin 1 (XOUT) left
    sh.wire(xo, sh.P(rx, 1))
    sh.wire(sh.P(rx, 2), (cx, xo[1]), sh.P(Yc, 3))
    sh.place(c2, cx, xo[1] + 3.81, fields='right')
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    en = sh.P(U, 3)
    ey = 109.22
    sh.wire(en, (170.18, en[1]), (170.18, ey), (162.56, ey), (152.4, ey), (142.24, ey), (127.0, ey))
    sh.glabel((127.0, ey), 'S3_EN', 'L', 'bidirectional')
    sh.place(K['R_EN'], 162.56, ey - 3.81, fields='right')
    sh.sup(sh.P(K['R_EN'], 1), '+3V3')
    sh.place(K['C_EN'], 152.4, ey + 3.81, fields='right')
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    # IO0 (BOOT): button + the auto-program transistor
    io0 = sh.P(U, 27)
    sh.wire(io0, (147.32, io0[1]), (137.16, io0[1]))
    sh.glabel((137.16, io0[1]), 'S3_IO0', 'L', 'bidirectional')
    sh.place(K['SW_S3BOOT'], 147.32, io0[1] + 5.08, rot=270, fields='left')
    sh.gnd(sh.P(K['SW_S3BOOT'], 2))
    # IO4 / IO5: RUN / BOOTSEL of the RP2354A
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    sh.place(K['R_CPRST'], 172.72, rst[1] - 3.81, fields='left')
    sh.wire(rst, (172.72, rst[1]), (167.64, rst[1]))
    sh.sup(sh.P(K['R_CPRST'], 1), '+3V3')
    sh.glabel((167.64, rst[1]), 'CP_RST', 'L')
    sh.gnd(sh.P(U, 3))
    sh.gnd(sh.P(U, 23), 2.54, rot=90)                      # /CTS tied low
    nc_unused(sh, U)
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    gq = sh.P(K['C_CONS'], 2)
    sh.wire(gq, (gq[0] - 5.08, gq[1]))
    sh.flag((gq[0] - 5.08, gq[1]), 'GND')
    # console 5 V sense for the RP (GPIO27): 0.6 x CONS_5V, filtered
    vh, vl, vc = K['R_VSH'], K['R_VSL'], K['C_VS']
    sh.place(vh, 53.34, y5 - 7.62 - 3.81, rot=180, fields='left')   # pin 1 (CONS_5V) down
    sh.wire((53.34, y5), sh.P(vh, 1))
    nd = sh.P(vh, 2)
    vy = nd[1] - 2.54
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    sh.gnd(sh.P(vl, 2))
    sh.place(vc, 73.66, vy + 3.81, fields='right')
    sh.gnd(sh.P(vc, 2))
    sh.glabel((83.82, vy), 'VSENSE', 'R', 'output')
    # USB VBUS -> gate, and through the SS34 onto +5V
    Dv = K['D_VBUS']
    sh.place(Dv, 83.82, yv, rot=180, fields='below')
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
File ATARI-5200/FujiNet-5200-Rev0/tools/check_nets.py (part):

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      PIN_RP2040_RUN/BOOTSEL when the pinmap does not define them
and checks every GPIO of both chips against the pin *functions* the netlist reports (GPIOn on
the RP2354B, IOn on the S3, An/Yn on the '541), the 5200 36-pin edge map (its own copy of the
pinout, from Atari's CX5200 Field Service Manual), the 5 V-tolerance rule for GPIO40-47, the PHI2
buffer, the supply sense dividers, the interlock, the three-source power path, and the edge
footprint's faces, pin-1 end and short interlock fingers.  The enable logic itself is
check_glue.py's.
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    chk('GP%d (PHI2_RP): the RP and the buffer only' % P['PHI2'], not others(rp(P['PHI2']), {U1, U17} | tps))

    # ---- the RP's own outputs and inputs ----
    pwr_ok_pin = rp(P['PWROK'])
    bufen = rp(P['BUFEN'])
    chk('GP%d (BUF_EN) -> a 74HCT glue input' % P['BUFEN'], glue_in(bufen))
    pd = pulldown(bufen)
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        hdr is not None and node_net.get((hdr, '1')) == rp(P['DBG_TX']) and node_net.get((hdr, '2')) == rp(P['DBG_RX'])
        and node_net.get((hdr, '3')) == 'GND')

    # ---- interlock: 18-36 shorted by the solder jumper; the DNP low-side switch from GPIO28 beside it ----
    ia, ib = edge[18], edge[36]
    jp = [r for r, (v, fp) in parts.items() if r.startswith('JP') and
          {node_net.get((r, '1')), node_net.get((r, '2'))} == {ia, ib}]
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            all(r in dnp for r in [r for r in parts if re.match(r'R\d+$', r) and through_r(gate, v5) and
                                   {node_net.get((r, '1')), node_net.get((r, '2'))} == {gate, v5}]))

    # ---- GPIO40-47 are not 5 V tolerant: the ADC sense or the 3.3 V debug header only ----
    for g in range(40, 48):
        n = rp(g)
        if unconn(n):
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        chk('GP%d (%s): nothing but passives or the 3.3 V debug header on the net' % (g, n), not bad)
        chk('GP%d (%s): never an edge signal' % (g, n), n not in edge.values())

    # ---- supply sense: edge pin 26 (VR1) -> divider -> ADC (GPIO40) ----
    cons = sig['PWR']
    adc = rp(P['VSENSE'])
    top, bot = through_r(cons, adc), through_r(adc, 'GND')
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            'current)' % (5.25 * r), 5.25 * r < VCC_MIN)
    pwr_ok = inv(inv(vsense))
    chk('PWR_OK = !!VSENSE on the Schmitt', pwr_ok is not None)
    chk('PWR_OK -> GP%d' % P['PWROK'], pwr_ok == pwr_ok_pin)
    chk('PWR_OK -> the glue', glue_in(pwr_ok))
    for r in sorted(glue):
        vcc, gnd = ('20', '10') if r == BUF else ('5', '3') if r == U17 else ('14', '7')
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    chk('RP USB_DP -> 27R -> S3 USB_D+ (IO20)', through_r(func_net.get((U1, 'USB_DP')), func_net.get((S3, 'USB_D+'))) == '27R')
    chk('RP USB_DM -> 27R -> S3 USB_D- (IO19)', through_r(func_net.get((U1, 'USB_DM')), func_net.get((S3, 'USB_D-'))) == '27R')
    print('note: S3 pins from %s' % PINMAP)
    run_io, bsel_io = define(PINMAP, 'PIN_RP2040_RUN', -2), define(PINMAP, 'PIN_RP2040_BOOTSEL', -2)
    if run_io == -2 or bsel_io == -2:
        run_io, bsel_io = define(PINMAP_RUN, 'PIN_RP2040_RUN'), define(PINMAP_RUN, 'PIN_RP2040_BOOTSEL')
        print('note: %s does not define PIN_RP2040_RUN/BOOTSEL; using fujiversal-intv.h (IO%d/IO%d)'
              % (os.path.basename(PINMAP), run_io, bsel_io))
    run, ss = func_net.get((U1, 'RUN')), func_net.get((U1, '~{QSPI_SS}'))
    chk('S3 IO%d (PIN_RP2040_RUN) -> 1k -> RP RUN' % run_io, through_r(s3(run_io), run) == '1k')
    chk('S3 IO%d (PIN_RP2040_BOOTSEL) -> 1k -> RP QSPI_SS' % bsel_io, through_r(s3(bsel_io), ss) == '1k')
    chk('RUN pull-up to the IO rail', through_r(run, v33io) == '10k')
    chk('QSPI_SS pull-up to the IO rail', through_r(ss, v33io) == '10k')
    for f in ('QSPI_SCLK', 'QSPI_SD0', 'QSPI_SD1', 'QSPI_SD2', 'QSPI_SD3'):
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            if ref == U1 and f in ('IOVDD', 'QSPI_IOVDD', 'USB_OTP_VDD', 'ADC_AVDD', 'VREG_VIN'):
                chk('RP %s (pin %s) on %s' % (f, pin, v33io), n == v33io)
            if ref == U1 and f == 'DVDD':
                chk('RP DVDD (pin %s) on DVDD' % pin, n == func_net.get((U1, 'VREG_FB')))
            if ref == U1 and f in ('GND', 'VREG_PGND'):
                chk('RP %s (pin %s) on GND' % (f, pin), n == 'GND')
    for f in ('SWCLK', 'SWDIO', 'RUN'):
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
    # ---- S3 pins: the pinmap ----
    sd = {k: define(PINMAP, 'PIN_SD_HOST_' + k) for k in ('CS', 'SCK', 'MISO', 'MOSI')}
    led_strip = define(PINMAP, 'PIN_LED_STRIP')
    uart_rx, uart_tx = define(PINMAP, 'PIN_UART0_RX'), define(PINMAP, 'PIN_UART0_TX')
    card = define(PINMAP, 'PIN_CARD_DETECT', -1)
    chk('SD CS  IO%d -> microSD DAT3/CS' % sd['CS'], s3(sd['CS']) == node_net.get((J2, '2')))
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              '(pulled up) as the 7800 / NES / SMS boards do, unused by the firmware' % (os.path.basename(PINMAP), cd_io))
    ws_din = node_net.get((WS, '3'))
    chk('LED strip IO%d -> R -> WS2812 DIN' % led_strip, through_r(s3(led_strip), ws_din) is not None)
    chk('PIN_UART0_TX/RX are the module TXD0/RXD0 pads (GPIO43/44)', (uart_tx, uart_rx) == (43, 44))
    chk('S3 TXD0 -> CP2102N RXD', func_net.get((S3, 'TXD0')) == func_net.get((UCP, 'RXD')))
    chk('S3 RXD0 <- CP2102N TXD', func_net.get((S3, 'RXD0')) == func_net.get((UCP, 'TXD')))
    contract = set(sd.values()) | {led_strip, run_io, bsel_io, 19, 20, 0} | ({card} if card >= 0 else {cd_io})
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
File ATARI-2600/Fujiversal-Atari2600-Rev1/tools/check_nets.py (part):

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  pico/atari-2600/firmware/include/vcs_pins.h        ADDR_PIN, ADDR_BITS, D0_PIN, DIR_PIN
  pico/atari-2600/firmware/boards/fujivcs.cmake      PICO_PLATFORM, PICO_FLASH_SIZE_BYTES
  pico/atari-2600/firmware/boards/fujivcs.h          -> boards/pico.h (LED = GP25)
  include/pinmap/fujiversal-atari2600.h              S3 SD/LED/UART/RUN/BOOTSEL pins
and checks every one of them, plus the Atari 2600 edge map, against the pin
*functions* the netlist reports (GPIOn on the RP2354A, IOn on the S3).  Rev1
wires the bus straight from the fingers to the RP's 5 V-tolerant pads, so
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EDGE = {1: 'A7', 2: 'A6', 3: 'A5', 4: 'A4', 5: 'A3', 6: 'A2', 7: 'A1', 8: 'A0',
        9: 'D0', 10: 'D1', 11: 'D2', 12: 'GND', 13: 'D3', 14: 'D4', 15: 'D5', 16: 'D6',
        17: 'D7', 18: 'A12', 19: 'A10', 20: 'A11', 21: 'A9', 22: 'A8', 23: '+5V', 24: 'GND'}
# RP2350 datasheet Table 1427: on the QFN-60 package GPIO0-25 are "Digital IO (FT)"
# (5.5 V with IOVDD at 3.3 V); GPIO26-29 share the ADC and are not 5 V tolerant.
FT_GPIOS = range(26)

fails = 0
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    chk('fujivcs.h is a pico-family board (PICO_DEFAULT_LED_PIN = GP25)', 'boards/pico' in bh)
    pm = 'include/pinmap/fujiversal-atari2600.h'
    sd = {k: define(pm, 'PIN_SD_HOST_' + k) for k in ('CS', 'SCK', 'MISO', 'MOSI')}
    led_strip = define(pm, 'PIN_LED_STRIP')
    run_io, bsel_io = define(pm, 'PIN_RP2040_RUN'), define(pm, 'PIN_RP2040_BOOTSEL')
    u0rx, u0tx = define(pm, 'PIN_UART0_RX'), define(pm, 'PIN_UART0_TX')

    # ---- edge -> RP2354A, direct ----
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        chk('VSENSE at a 4.5 V console (%.2f V) above VIH 2.0 V' % v, v >= 2.0)

    # ---- RP2354A support ----
    chk('GP25 (PICO_DEFAULT_LED_PIN) -> R -> LED', through_r(rp(25), 'RP_LED_A') is not None)
    chk('RP USB_DP -> 27R -> S3 USB_D+ (IO20)', through_r(func_net.get((U1, 'USB_DP')), func_net.get((U2, 'USB_D+'))) == '27R')
    chk('RP USB_DM -> 27R -> S3 USB_D- (IO19)', through_r(func_net.get((U1, 'USB_DM')), func_net.get((U2, 'USB_D-'))) == '27R')
    run, ss = func_net.get((U1, 'RUN')), func_net.get((U1, '~{QSPI_SS}'))
    chk('S3 IO%d (PIN_RP2040_RUN) -> 1k -> RP RUN (active low, no inverter)' % run_io, through_r(s3(run_io), run) == '1k')
    chk('S3 IO%d (PIN_RP2040_BOOTSEL) -> 1k -> RP QSPI_SS' % bsel_io, through_r(s3(bsel_io), ss) == '1k')
    chk('RUN pull-up to the RP rail', through_r(run, '+3V3_RP') == '10k')
    chk('QSPI_SS pull-up to the RP rail', through_r(ss, '+3V3_RP') == '10k')
    for f in ('QSPI_SCLK', 'QSPI_SD0', 'QSPI_SD1', 'QSPI_SD2', 'QSPI_SD3'):
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        for pin, n in pins:
            chk('RP %s (pin %s) on +3V3_RP' % (f, pin), n == '+3V3_RP')
    chk('VREG_AVDD from +3V3_RP through 33R (datasheet Figure 19)', through_r('+3V3_RP', func_net.get((U1, 'VREG_AVDD'))) == '33R')
    for pin, n in rp_pins('DVDD') + rp_pins('VREG_FB'):
        chk('RP DVDD/VREG_FB (pin %s) on DVDD' % pin, n == 'DVDD')
    lx = func_net.get((U1, 'VREG_LX'))
    chk('VREG_LX -> 3.3uH -> DVDD', any(val == '3.3uH' and {node_net.get((r, '1')), node_net.get((r, '2'))} == {lx, 'DVDD'}
                                        for r, (val, _, _) in parts.items() if r.startswith('L')))
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
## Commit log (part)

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2020-05-10 Add schematics
2020-05-15 Fix cut off WROVER schematic
2020-05-25 Update WROVER schematic with some notes
2020-06-07 Schematics: Add v1.0 schematic and rename all so they are in order by date.
2020-07-05 Add CC-BY-SA LICENSE
2020-07-05 Add FujiNet 1.0 dir with 3D designs & schematic, move old schematics to Prototype dir
2020-07-17 Add PCB 3D files
2020-08-11 Reduce SIO Receptacle depth by 1.75mm
2020-08-11 Add 1.0 PCB 3D files
2020-08-11 Add official and complete FujiNet 1.0 design files
2020-08-15 Add OSHWA certification info and logos to PCB
2020-08-15 Update logo mark with missing 0 in UID
2020-08-18 Add SIO pin part numbers to BOM
2020-09-02 Add Diptrace libraries
2020-12-25 Add v1.3 hardware design. Fixes #1, #2, #3
2021-01-02 Update v1.3 README
2021-01-02 Update v1.3 Plug with added support for pins & no longer has domed holes on the mating end.
2021-01-15 Add image of bodge for issue #5
2021-01-15 Fix CP2102 Reset bug in v1.3 design
2021-01-15 Update README and CP2102 fix image cuz I can't count
2021-01-16 Add v1.3 PCB STEP file
2021-01-24 Add resistor divider fix for v1.3 board
2021-02-13 Update v1.3 fix information
2021-03-14 Add v1.5 design files. Fixes #5. Move old versions to subdir
2021-03-14 More file cleanup
2021-03-14 Update schematic & README: Reduce capacitance for auto-reset/EN
2021-03-28 Add Diptrace library for Commodore patterns
2021-03-28 Add Diptrace component library for Commodore ports
2021-04-11 More descriptive change log
2021-05-03 Fujinet Version 1.0: Added insert for plug to minimize possibility of ping breaking when not evenly inserted.
2021-10-14 Add FujiNet576NUC design files
2021-11-28 Add FujiNet v1.6 design files
2021-12-15 Add Coleco ADAM prototype schematic
2022-02-24 Update ADAM schematic
2022-03-07 Add ADAM DEVKITC Schematic
2022-04-01 Rearrange dir structure to accomodate multiple platforms
2022-04-14 Add ADAM FujiNet v1.0 design
2022-06-13 Fix cut off schematic image
2022-07-23 Add FujiApple Rev00 Hardware Design
2022-07-24 A2: change resistor divider for HDSEL
2022-08-05 A2: add 3D model of Rev 00
2022-09-18 Add RS232 prototype
2022-10-06 AppleII: add DB19 Adapter
2022-10-06 Update Readme.md
    Added images
2022-12-04 Add STL files for Apple II case
2023-01-19 ATARI: add v1.7 hardware
2023-03-22 FujiApple Rev00 SPI Fix
2023-03-22 FujiaApple Rev00 SPI Fix README
2023-03-22 Add Lynx FujiNet DEVKITC Schematic
2023-06-02 Add FujiApple Rev000
2023-08-11 Add FujiLynx Prototype
2023-08-24 atari: update v1.7 XE front case, fix disconnected screw posts near sio plug
2023-11-29 Add FujiApple Rev1 Schematic
2023-12-18 Add DB19 to IDC20F Adapter
2023-12-25 Add FujiApple Rev1 hardware design files
2023-12-27 Add FujiApple Rev1 PickNPlace & BOM as CSV
2023-12-28 Update BOM CSV and Pick-N-Place File
2023-12-28 Add some JLCPCB part numbers to BOM CSV
2023-12-29 Finish adding JLCPCB part number to FujiApple BOM
2024-02-18 Add FujiApple Rev1.1
2024-02-18 Add Atari v1.7.1
2024-02-20 Fix unconnected 12V trace on Apple II DB19 Female PCB
2024-02-26 AppleII: fix link to wiki in README for hardware
2024-03-09 Reorganize Apple II and add new designs
2024-03-09 Fix docs directory
2024-03-10 Update Apple II docs
2024-03-10 Fix images links in docs
2024-03-29 Atari: add devkit-shield and move old versions
2024-03-31 Add Coco designs
2024-04-02 RC2014: Add last prototype (Rev 0.3)
2024-04-18 Add Apple Mac 68k FujiNet
2024-04-18 Add AliExpress BOM
2024-04-18 Fix README typo
2024-04-22 Rework instructions for multiple baud rate selection
2024-06-23 Mirror '2' and '40' indicators so they are readable
2024-06-23 Revert "Mirror '2' and '40' indicators so they are readable"
    This reverts commit 8205e6bc94a8408d7df05aae4ad7f4186c382163.
2024-06-23 Mirror '2' and '40' text so it is readable on the backside of the PCB
2024-08-17 Apple2: Updated DB-19 adapter to Rev1.1
2024-08-26 Add Coco Rev0000 version
2024-08-26 Move Rev000 back from Old directory to deal with merge of PCB change
2024-10-01 Fix BOM for Apple II DevKit flavors, should be LSF0204PWR (no D)
2024-10-06 Add Apple III adapter board
2024-10-06 Update Apple III adapter README
2024-10-21 Add connector sleeve for Apple III adapter
2025-02-03 Add Dragon ROM and cabling docs for CocoFuji
2025-03-01 RS232: add Rev000 with DB9F
2025-03-06 Fix images of old hardware versions
    Additionally, make resized images link to the full-size version.
    Also fixes one typo.
2025-03-14 replace level-shifter component
2025-03-14 fix naming of RS232-Rev00
2025-03-18 RS232: Update Rev000 to support both TSSOP & SSOP on same PCB
2025-09-03 Add RS232 Rev1 Hardware
2025-09-03 Add RS232 schematic image
2025-09-05 Add RS232 BOM and fix gitignore to allow CSV
2025-09-06 Add missing RS232 CSV files. Fix screw link in RS232 README
2025-09-12 Update dragon support
2025-10-22 Add RS232-Rev1b: push-push MicroSD socket
2025-11-09 [h89] add H89 hardware schematic and related datasheets and programming info.
2026-03-13 Add MSX prototype schematics and pics
2026-03-13 MSX: Update README.md
2026-03-13 MSX: Add PDF schematic to README
2026-06-15 Dragon rom update
    Suppress interrupts while processing drivewire commands to resolve issues
    with glitches on directory entry fetches etc.
